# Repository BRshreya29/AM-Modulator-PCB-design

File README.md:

# Amplitude Modulation and Demodulation Design

This repository contains my project on Printed Circuit Board deisgn The project involves designing an **Amplitude Modulator and Demodulator** on a single PCB, demonstrating the principles of amplitude modulation (AM) and demodulation.

## Objective
To design and simulate a circuit that performs:
- **Amplitude Modulation (AM)**: Modulates a message signal onto a carrier signal, with adjustable modulation index.
- **Amplitude Demodulation**: Extracts the original message signal from the modulated AM signal, with a customizable low-pass filter (LPF) cutoff frequency.

## Overview
The design process involved the following steps:
1. **Circuit Simulation**: The circuit was simulated in LTspice software.
2. **PCB Design**: Schematic and layout routing were completed using PCB design tools. Design Rule Check (DRC) shows zero errors.
3. **Validation**: Both modulation and demodulation functionalities were verified under ideal simulation conditions.

## Circuit Description
### Purpose
The circuit demonstrates the modulation of an input message signal onto a carrier signal and the recovery of the message signal through demodulation. It allows for parameter adjustments, such as the modulation index and LPF cutoff frequency, for better understanding and optimization.

### Working Conditions
- **Simulation Environment**: LTspice
- **Inputs**:
  - Carrier Signal: Sine wave, frequency 100 kHz to 1 MHz, amplitude 1–5 V p-p.
  - Message Signal: Sine wave, frequency 20 Hz to 20 kHz, amplitude 0.5–5 V p-p.
- **Outputs**:
  - Modulated AM signal.
  - Demodulated message signal (post-LPF).
- **Power Supply**: 
  - +12V and -12V DC for circuit components.
  - Ground (GND) common for all interconnected circuits.

### Constraints
- **Load Impedance**:
  - Modulator output: Ideal resistive load (>1 kΩ). Used 3.9 kΩ in the design.
  - Demodulator output: Resistor-capacitor (R-C) network satisfying the relation $f_c = \frac{1}{2\pi RC}$ for LPF.

## Power Consumption
### AM Modulator
- Load Resistor (R<sub>L</sub>): 3.9 kΩ
  - Power dissipation: $P_{R_L} = \frac{V^2}{R} \approx 36.9$ mW
- Modulator IC (MC1496):
  - Power consumption: $P_{IC} = V_{CC} \cdot I_{CC} \approx 24$ mW
- **Total Modulator Power**: $P_{modulator} \approx 60.9$ mW

### AM Demodulator
- Power dissipation depends on the modulated wave's amplitude ($V_m$) and resistor value ($R$). Capacitors do not dissipate power directly.

### Modulation Index
The modulation index (μ) affects the total power of the AM signal:
\[
P_{AM} = P_c \left( 1 + \frac{\mu^2}{2} \right)
\]
where $P_c$ is the carrier power.

## PCB Design
The PCB design includes:
1. **Modulator Block**: Accepts carrier and message signals. Outputs an AM signal with adjustable modulation index.
2. **Demodulator Block**: Accepts the modulated AM signal. Outputs the demodulated message signal post-LPF.

The schematic and PCB layout were completed with no errors in the DRC.

## PCB Schematic and Layout

Below are the images of the designed PCB schematic and layout:

### PCB Schematic

### PCB Layout

## Repository Structure
```
.
├── PCB_Design            # PCB schematic and layout files
├── Documentation         # Detailed report and circuit explanations
├── CAM Outputs           # Gerber Files for PCB Printing
└── README.md             # This file
```

## Key Features
- Adjustable modulation index in the modulator block.
- Customizable LPF cutoff frequency in the demodulator block.
- Accurate simulation results using LTspice.
- Zero-error PCB design verified using DRC.

## Conclusion
This project included circuit design, implementation on bread-board, circuit simulation results, and circuit diagram included in the report.

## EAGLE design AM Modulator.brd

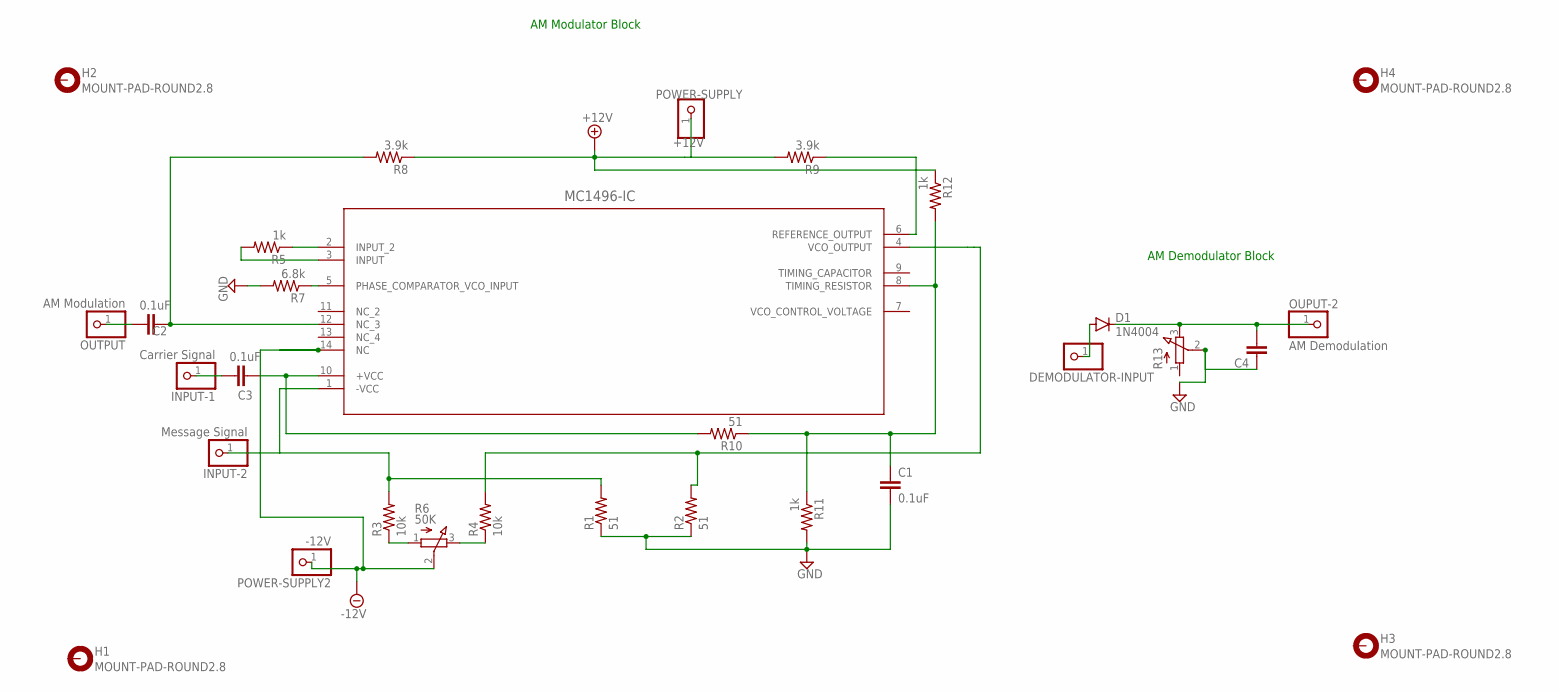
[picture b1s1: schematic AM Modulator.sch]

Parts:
C1, C2, C3: 0.1uF; C025-024X044
C4: C-EU025-024X044; C025-024X044
D1: 1N4004; DO41-10
DEMODULATOR-INPUT: PINHD-1X1; 1X01
H1, H2, H3, H4: MOUNT-PAD-ROUND2.8; 2,8-PAD
INPUT-1: Carrier Signal; 1X01
INPUT-2: Message Signal; 1X01
MC1496-IC: LM565CN; DIP_565CN_TEX
OUPUT-2: AM Demodulation; 1X01
OUTPUT: AM Modulation; 1X01
POWER-SUPPLY: +12V; 1X01
POWER-SUPPLY2: -12V; 1X01
R1, R2, R10: 51; 0207/10
R3, R4: 10k; 0207/10
R5, R11, R12: 1k; 0207/10
R6: 50K; 3RP/1610N
R7: 6.8k; 0207/10
R8, R9: 3.9k; 0207/10
R13: 3RP/1610N

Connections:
+12V: POWER-SUPPLY.1, R8.1, R9.2, R12.1
-12V: MC1496-IC.14 (NC), POWER-SUPPLY2.1, R6.2 (S)
GND: C1.2, C4.1, R1.1, R2.1, R7.2, R11.2, R13.2 (S)
unnamed: INPUT-2.1, MC1496-IC.1 (-VCC), R1.2, R3.2
unnamed: MC1496-IC.4 (VCO_OUTPUT), R2.2, R4.2
unnamed: R3.1, R6.1 (A)
unnamed: R4.1, R6.3 (E)
unnamed: C1.1, MC1496-IC.8 (TIMING_RESISTOR), R10.1, R11.1, R12.2
unnamed: MC1496-IC.5 (PHASE_COMPARATOR_VCO_INPUT), R7.1
unnamed: MC1496-IC.6 (REFERENCE_OUTPUT), R9.1
unnamed: C2.1, MC1496-IC.12 (NC_3), R8.2
unnamed: MC1496-IC.2 (INPUT_2), R5.1
unnamed: MC1496-IC.3 (INPUT), R5.2
unnamed: C3.2, MC1496-IC.10 (+VCC), R10.2
unnamed: C2.2, OUTPUT.1
unnamed: C3.1, INPUT-1.1
unnamed: C4.2, D1.C, OUPUT-2.1, R13.3 (E)
unnamed: D1.A, DEMODULATOR-INPUT.1

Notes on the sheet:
AM Modulator Block
AM Demodulator Block

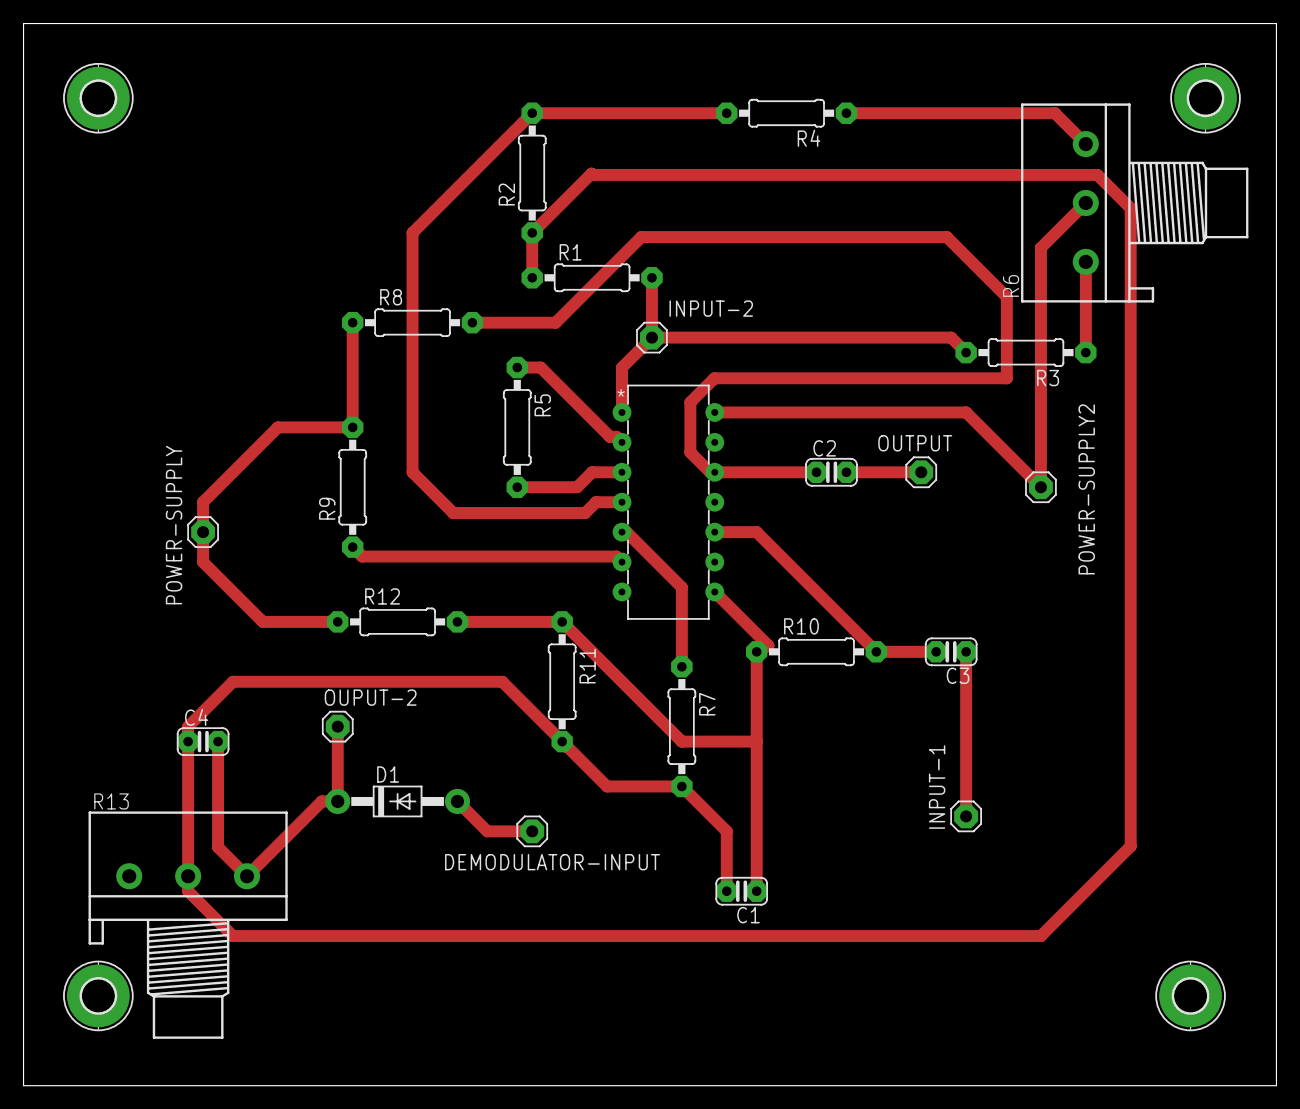
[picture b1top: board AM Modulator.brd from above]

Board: 2 copper layers, 106.4 x 90.2 mm, 30 parts (0 on the bottom side), 18 nets.

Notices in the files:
parts and their libraries:
COPYRIGHT: Copyright (C) 2024 Ultra Librarian. All rights reserved.
